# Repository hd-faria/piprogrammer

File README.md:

# piprogrammer
This hat was designed based on Wren's Pi400-Pico-Plate, but since I don't have a Pi400, just a Raspberry Pi 4 4GB, I needed to make some changes. Also added an extra button and a JST(Qwiic) connector, which is connected to floating header because I wanted the flexibility to move I2C. Also added a 50" JTAG/SWD header footprint in hopes that I can use the Pi4 to program target devices other than RP2040 based boards, I remember to have seem some adafruit/learn post on this kind of subject some time ago.

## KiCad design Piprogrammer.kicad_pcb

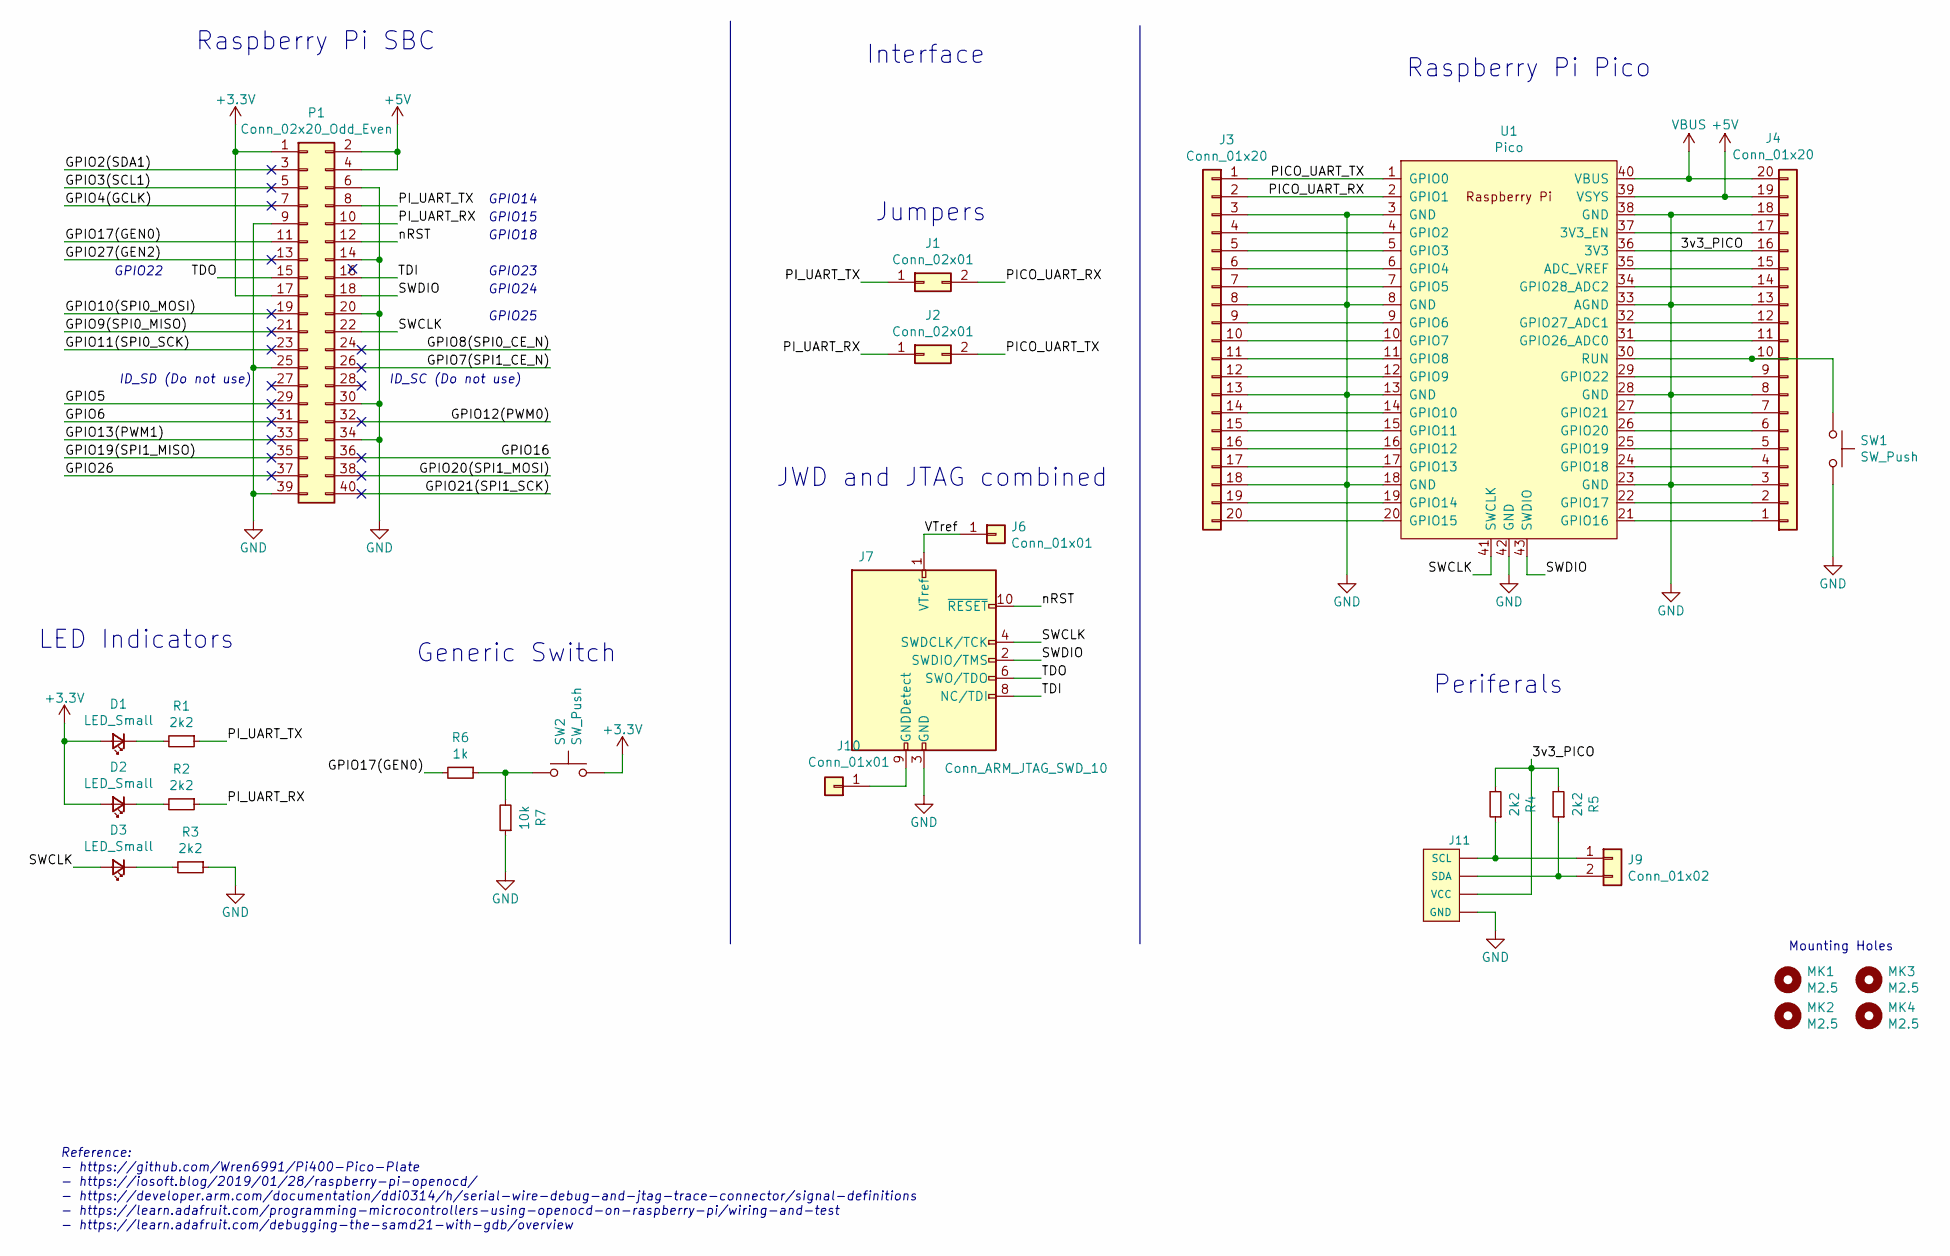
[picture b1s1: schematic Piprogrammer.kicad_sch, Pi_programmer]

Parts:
D1, D2, D3: LED_Small; LED_0603_1608Metric_Pad1.05x0.95mm_HandSolder
J1, J2: Conn_02x01; PinHeader_2x01_P2.54mm_Vertical
J3, J4: Conn_01x20; PinSocket_1x20_P2.54mm_Vertical
J6, J10: Conn_01x01; PinSocket_1x01_P2.54mm_Vertical
J7: Conn_ARM_JTAG_SWD_10; PinHeader_2x05_P1.27mm_Vertical
J9: Conn_01x02; PinSocket_1x02_P2.54mm_Vertical
J11: QWIIC_CONNECTORJS-1MM; 1X04_1MM_RA
MK1, MK2, MK3, MK4: M2.5; MountingHole_2-5mm
P1: Conn_02x20_Odd_Even; Socket_Strip_Straight_2x20
R1, R2, R3, R4, R5: 2k2; R_0603_1608Metric_Pad0.98x0.95mm_HandSolder
R6: 1k; R_0603_1608Metric_Pad0.98x0.95mm_HandSolder
R7: 10k; R_0603_1608Metric_Pad0.98x0.95mm_HandSolder
SW1, SW2: SW_Push; SW_Push_1P1T_NO_CK_KSC6xxJ
U1: Pico; RPi_Pico_SMD_TH

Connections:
+3V3: D1.2 (A), D2.2 (A), P1.1, P1.17, SW2.2
+5V: J4.19, P1.2, P1.4, U1.39 (VSYS)
/3v3_PICO: J4.16, J11.2 (VCC), R4.2, R5.2, U1.36 (3V3)
/GPIO2(SDA1): P1.3
/GPIO3(SCL1): P1.5
/GPIO4(GCLK): P1.7
/GPIO5: P1.29
/GPIO6: P1.31
/GPIO7(SPI1_CE_N): P1.26
/GPIO8(SPI0_CE_N): P1.24
/GPIO9(SPI0_MISO): P1.21
/GPIO10(SPI0_MOSI): P1.19
/GPIO11(SPI0_SCK): P1.23
/GPIO12(PWM0): P1.32
/GPIO13(PWM1): P1.33
/GPIO16: P1.36
/GPIO17(GEN0): P1.11, R6.2
/GPIO19(SPI1_MISO): P1.35
/GPIO20(SPI1_MOSI): P1.38
/GPIO21(SPI1_SCK): P1.40
/GPIO26: P1.37
/GPIO27(GEN2): P1.13
/PICO_UART_RX: J1.2, J3.2, U1.2 (GPIO1)
/PICO_UART_TX: J2.2, J3.1, U1.1 (GPIO0)
/PI_UART_RX: J2.1, P1.10, R2.1
/PI_UART_TX: J1.1, P1.8, R1.1
/SWCLK: D3.2 (A), J7.4 (SWDCLK/TCK), P1.22, U1.41 (SWCLK)
/SWDIO: J7.2 (SWDIO/TMS), P1.18, U1.43 (SWDIO)
/TDI: J7.8 (NC/TDI), P1.16
/TDO: J7.6 (SWO/TDO), P1.15
/VTref: J6.1, J7.1 (VTref)
/nRST: J7.10 (~RESET), P1.12
GND: J3.3, J3.8, J3.13, J3.18, J4.3, J4.8, J4.13, J4.18, J7.3 (GND), J7.5 (GND), J11.1 (GND), P1.6, P1.9, P1.14, P1.20, P1.25, P1.30, P1.34, P1.39, R3.1, R7.1, SW1.2, U1.3 (GND), U1.8 (GND), U1.13 (GND), U1.18 (GND), U1.23 (GND), U1.28 (GND), U1.33 (AGND), U1.38 (GND), U1.42 (GND)
unnamed: D1.1 (K), R1.2
unnamed: D2.1 (K), R2.2
unnamed: D3.1 (K), R3.2
unnamed: J3.4, U1.4 (GPIO2)
unnamed: J3.5, U1.5 (GPIO3)
unnamed: J3.6, U1.6 (GPIO4)
unnamed: J3.7, U1.7 (GPIO5)
unnamed: J3.9, U1.9 (GPIO6)
unnamed: J3.10, U1.10 (GPIO7)
unnamed: J3.11, U1.11 (GPIO8)
unnamed: J3.12, U1.12 (GPIO9)
unnamed: J3.14, U1.14 (GPIO10)
unnamed: J3.15, U1.15 (GPIO11)
unnamed: J3.16, U1.16 (GPIO12)
unnamed: J3.17, U1.17 (GPIO13)
unnamed: J3.19, U1.19 (GPIO14)
unnamed: J3.20, U1.20 (GPIO15)
unnamed: J4.1, U1.21 (GPIO16)
unnamed: J4.2, U1.22 (GPIO17)
unnamed: J4.4, U1.24 (GPIO18)
unnamed: J4.5, U1.25 (GPIO19)
unnamed: J4.6, U1.26 (GPIO20)
unnamed: J4.7, U1.27 (GPIO21)
unnamed: J4.9, U1.29 (GPIO22)
unnamed: J4.10, SW1.1, U1.30 (RUN)
unnamed: J4.11, U1.31 (GPIO26_ADC0)
unnamed: J4.12, U1.32 (GPIO27_ADC1)
unnamed: J4.14, U1.34 (GPIO28_ADC2)
unnamed: J4.15, U1.35 (ADC_VREF)
unnamed: J4.17, U1.37 (3V3_EN)
unnamed: J7.9 (GNDDetect), J10.1
unnamed: J9.2, J11.3 (SDA), R5.1
unnamed: J9.1, J11.4 (SCL), R4.1
unnamed: R6.1, R7.2, SW2.1
VBUS: J4.20, U1.40 (VBUS)

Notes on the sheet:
GPIO22
LED Indicators
ID_SD (Do not use)
GPIO24
Raspberry Pi SBC
GPIO23
Generic Switch
GPIO25
GPIO14
Mounting Holes
Jumpers
Raspberry Pi Pico
Interface
GPIO18
Reference: - https://github.com/Wren6991/Pi400-Pico-Plate - https://iosoft.blog/2019/01/28/raspberry-pi-openocd/ - https://developer.arm.com/documentation/ddi0314/h/serial-wire-debug-and-jtag-trace-connector/signal-definitions - https://learn.adafruit.com/programming-microcontrollers-using-openocd-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
Periferals
ID_SC (Do not use)
GPIO15
JWD and JTAG combined

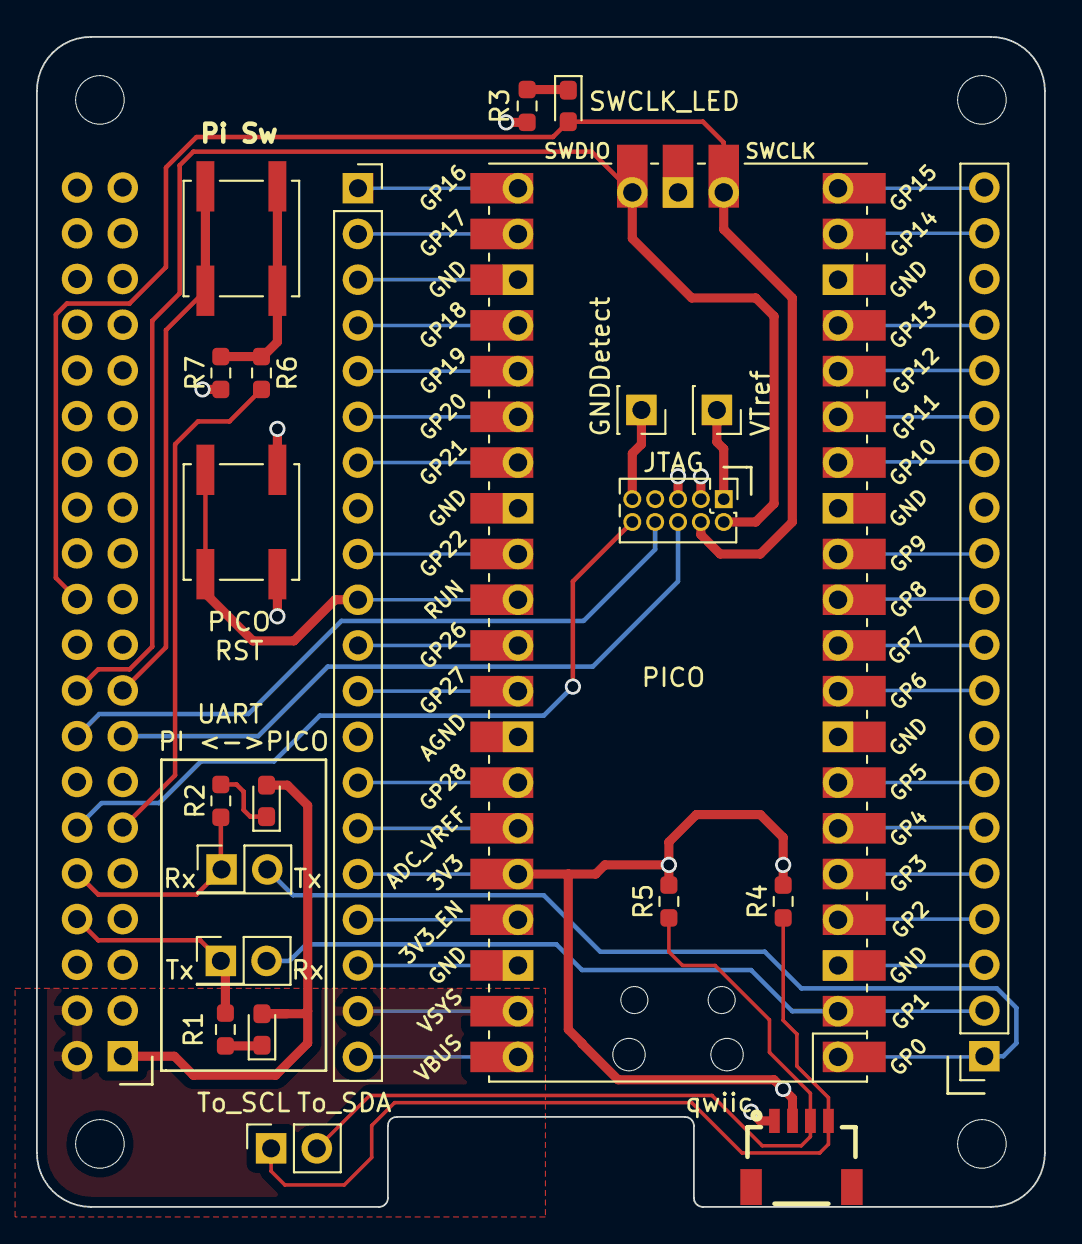
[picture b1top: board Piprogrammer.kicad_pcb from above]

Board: 2 copper layers, 56.0 x 65.0 mm, 27 parts (1 on the bottom side), 50 nets.

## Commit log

2021-10-27 add .gitignore
2021-10-27 add current content
2022-01-28 minor update em schematics presentation, update to kicad 6
2022-02-09 add pcb layers pdf
